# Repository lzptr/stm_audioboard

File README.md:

# stm_audioboard
STM32 based mixed signal audio board from phils lab mixed signal course (https://www.phils-lab.net/courses).

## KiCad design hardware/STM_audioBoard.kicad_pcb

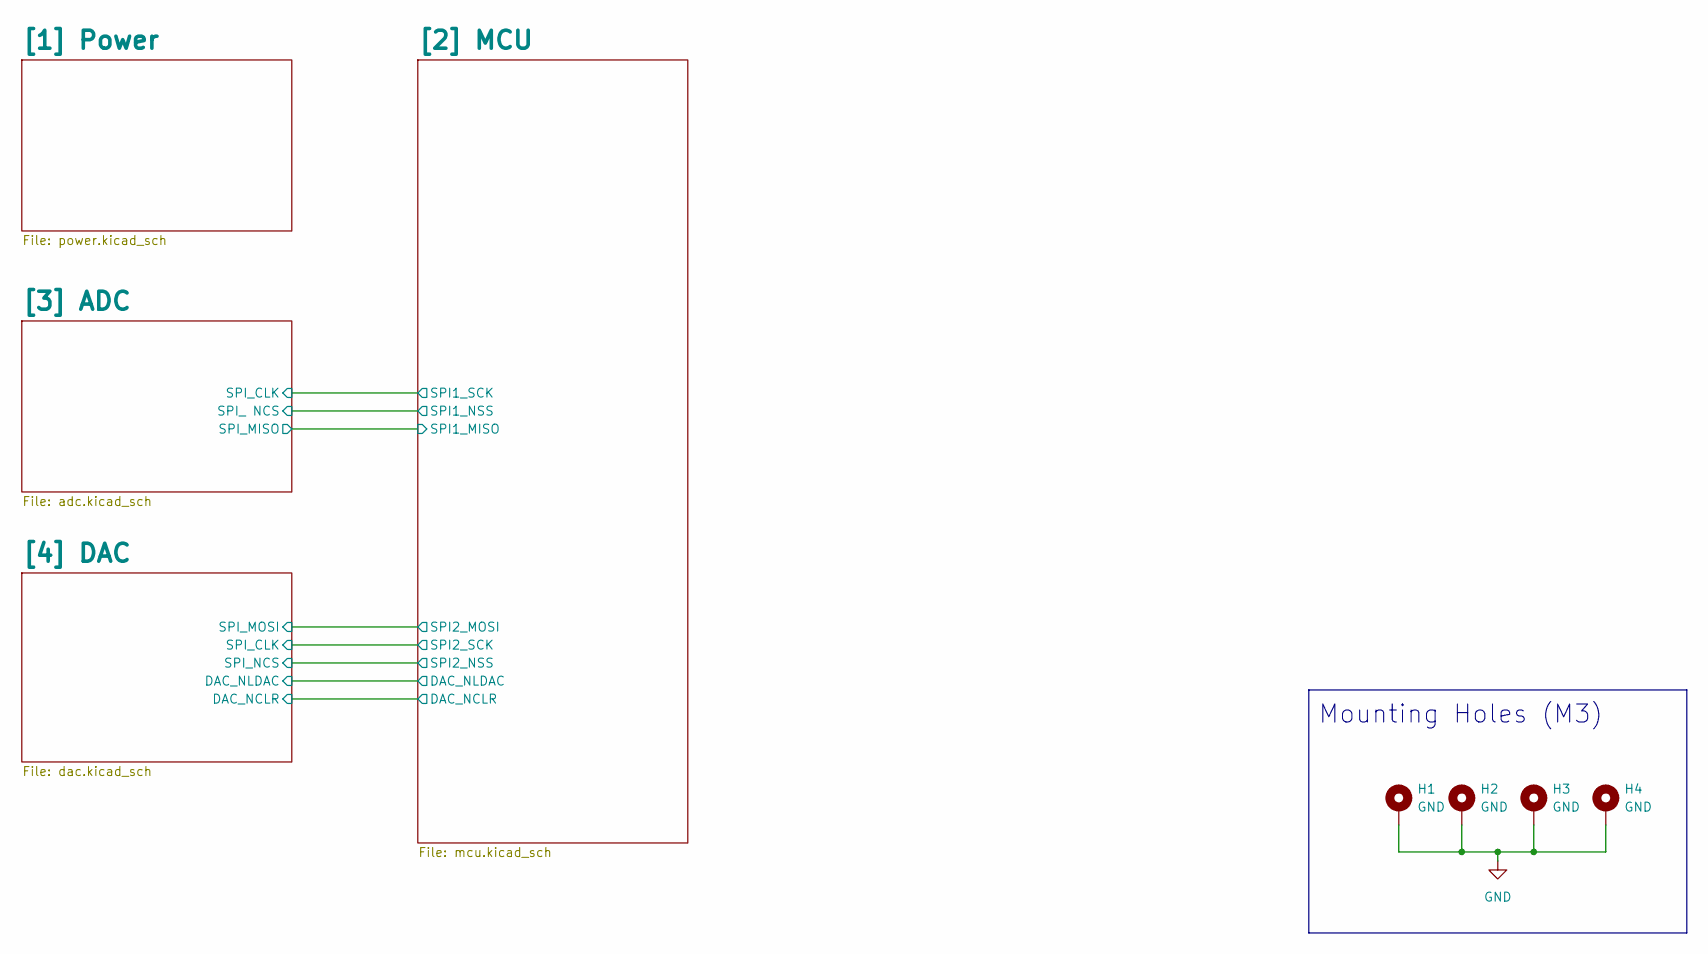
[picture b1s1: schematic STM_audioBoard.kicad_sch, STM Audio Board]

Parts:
H1, H2, H3, H4: GND; MountingHole_3.2mm_M3_Pad

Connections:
GND: H1.1, H2.1, H3.1, H4.1; also elsewhere on the board

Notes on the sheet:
Mounting Holes (M3)

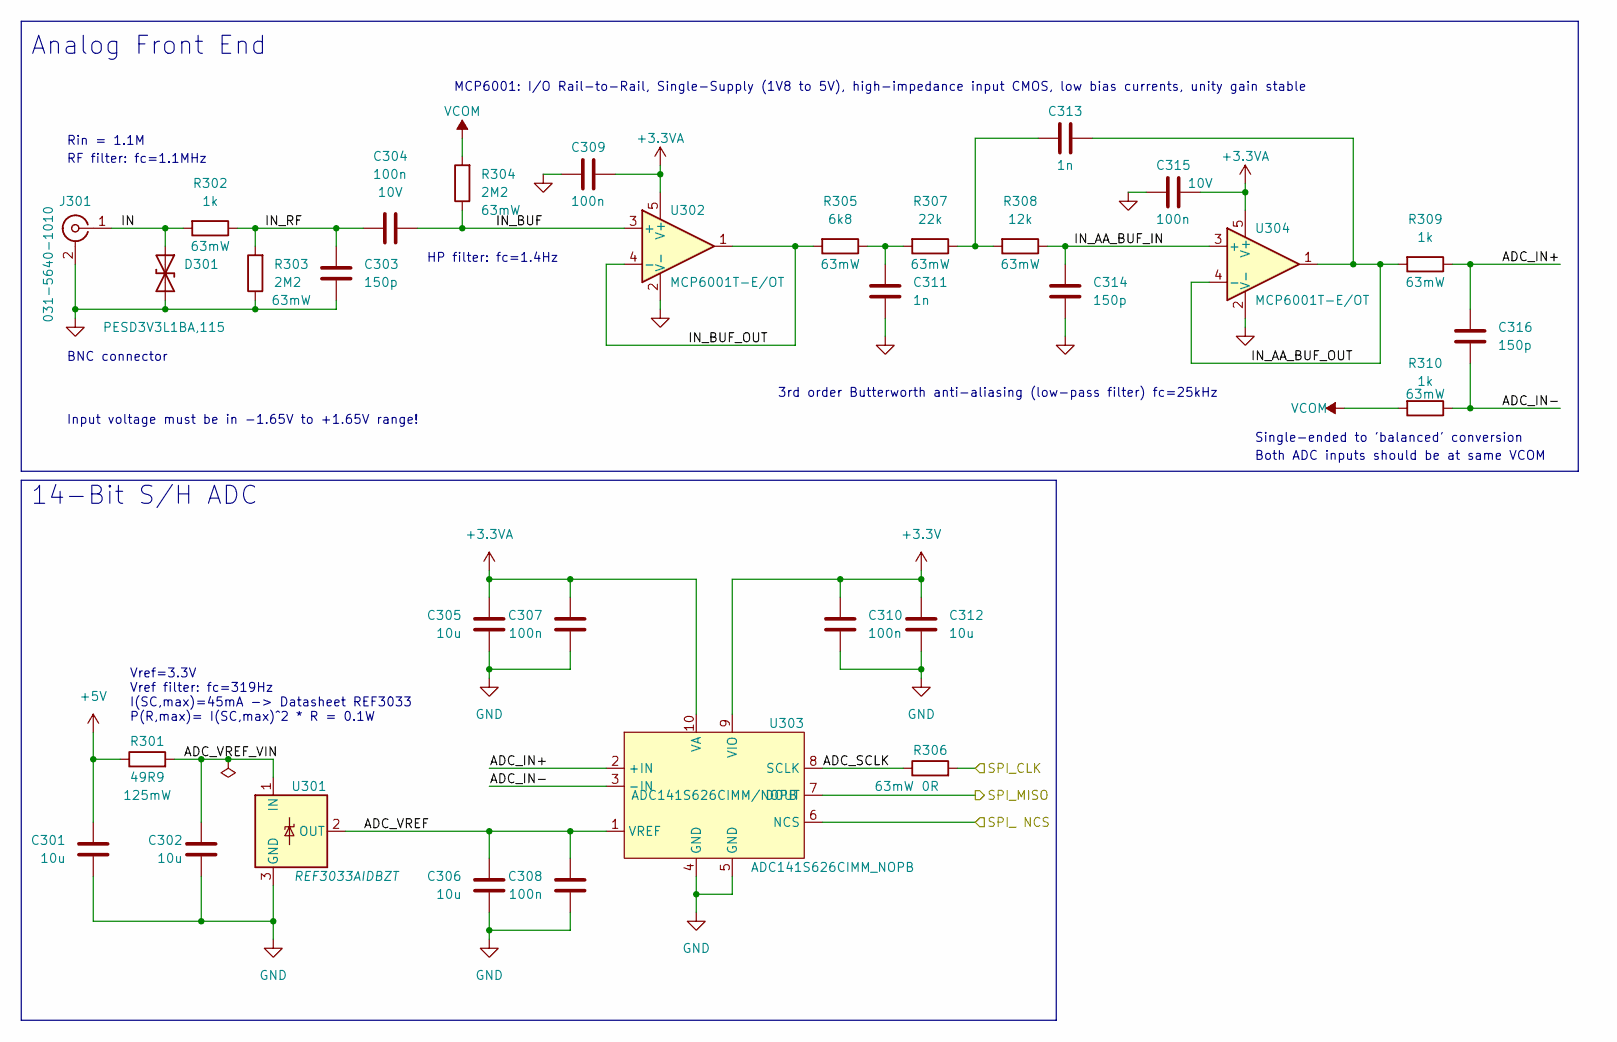
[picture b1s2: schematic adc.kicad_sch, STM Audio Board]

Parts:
C301, C302, C305, C306, C312: 10u; C_0603_1608Metric
C303, C314, C316: 150p; C_0402_1005Metric
C304, C307, C308, C309, C310, C315: 100n; C_0402_1005Metric; Rating 10V; MPN CC0402KRX5R6BB104
C311, C313: 1n; C_0402_1005Metric
D301: PESD3V3L1BA,115; D_SOD-323
J301: 031-5640-1010; AMPHENOL-BNC-031-5640-1010
R301: 49R9; R_0805_2012Metric; Rating 125mW
R302, R309, R310: 1k; R_0402_1005Metric; Rating 63mW
R303, R304: 2M2; R_0402_1005Metric; Rating 63mW
R305: 6k8; R_0402_1005Metric; Rating 63mW
R306: 0R; R_0402_1005Metric; Rating 63mW
R307: 22k; R_0402_1005Metric; Rating 63mW
R308: 12k; R_0402_1005Metric; Rating 63mW
U301: REF3033AIDBZT; SOT-23
U302, U304: MCP6001T-E/OT; SOT-23-5
U303: ADC141S626CIMM_NOPB; VSSOP-10; MPN ADC141S626CIMM/NOPB

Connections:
+3.3V: C310.1, C312.1, U303.9 (VIO); also elsewhere on the board
+3.3VA: C305.1, C307.1, C309.1, C315.1, U302.5 (V+), U303.10 (VA), U304.5 (V+); also elsewhere on the board
+5V: C301.1, R301.1; also elsewhere on the board
/[2] MCU/SPI1_MISO: U303.7 (DOUT); also elsewhere on the board
/[2] MCU/SPI1_NSS: U303.6 (NCS); also elsewhere on the board
/[2] MCU/SPI1_SCK: R306.2; also elsewhere on the board
/[3] ADC/ADC_IN+: C316.1, R309.1, U303.2 (+IN)
/[3] ADC/ADC_IN-: C316.2, R310.1, U303.3 (-IN)
/[3] ADC/ADC_SCLK: R306.1, U303.8 (SCLK)
/[3] ADC/ADC_VREF: C306.1, C308.1, U301.2 (OUT), U303.1 (VREF)
/[3] ADC/ADC_VREF_VIN: C302.1, R301.2, U301.1 (IN)
/[3] ADC/IN: D301.1 (A1), J301.1 (In), R302.2
/[3] ADC/IN_AA_BUF_IN: C314.1, R308.1, U304.3 (+)
/[3] ADC/IN_AA_BUF_OUT: C313.2, R309.2, U304.1, U304.4 (-)
/[3] ADC/IN_BUF: C304.1, R304.1, U302.3 (+)
/[3] ADC/IN_BUF_OUT: R305.2, U302.1, U302.4 (-)
/[3] ADC/IN_RF: C303.1, C304.2, R302.1, R303.2
GND: C301.2, C302.2, C303.2, C305.2, C306.2, C307.2, C308.2, C309.2, C310.2, C311.2, C312.2, C314.2, C315.2, D301.2 (A2), J301.2 (Ext), R303.1, U301.3 (GND), U302.2 (V-), U303.4 (GND), U303.5 (GND), U304.2 (V-); also elsewhere on the board
unnamed: C311.1, R305.1, R307.2
unnamed: C313.1, R307.1, R308.2
VCOM: R304.2, R310.2; also elsewhere on the board

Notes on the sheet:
RF filter: fc=1.1MHz
3rd order Butterworth anti-aliasing (low-pass filter) fc=25kHz
BNC connector
14-Bit S/H ADC
HP filter: fc=1.4Hz
Rin = 1.1M
MCP6001: I/O Rail-to-Rail, Single-Supply (1V8 to 5V), high-impedance input CMOS, low bias currents, unity gain stable
Input voltage must be in -1.65V to +1.65V range!
Vref=3.3V Vref filter: fc=319Hz I(SC,max)=45mA -> Datasheet REF3033 P(R,max)= I(SC,max)^2 * R = 0.1W
Analog Front End
Both ADC inputs should be at same VCOM
Single-ended to 'balanced' conversion

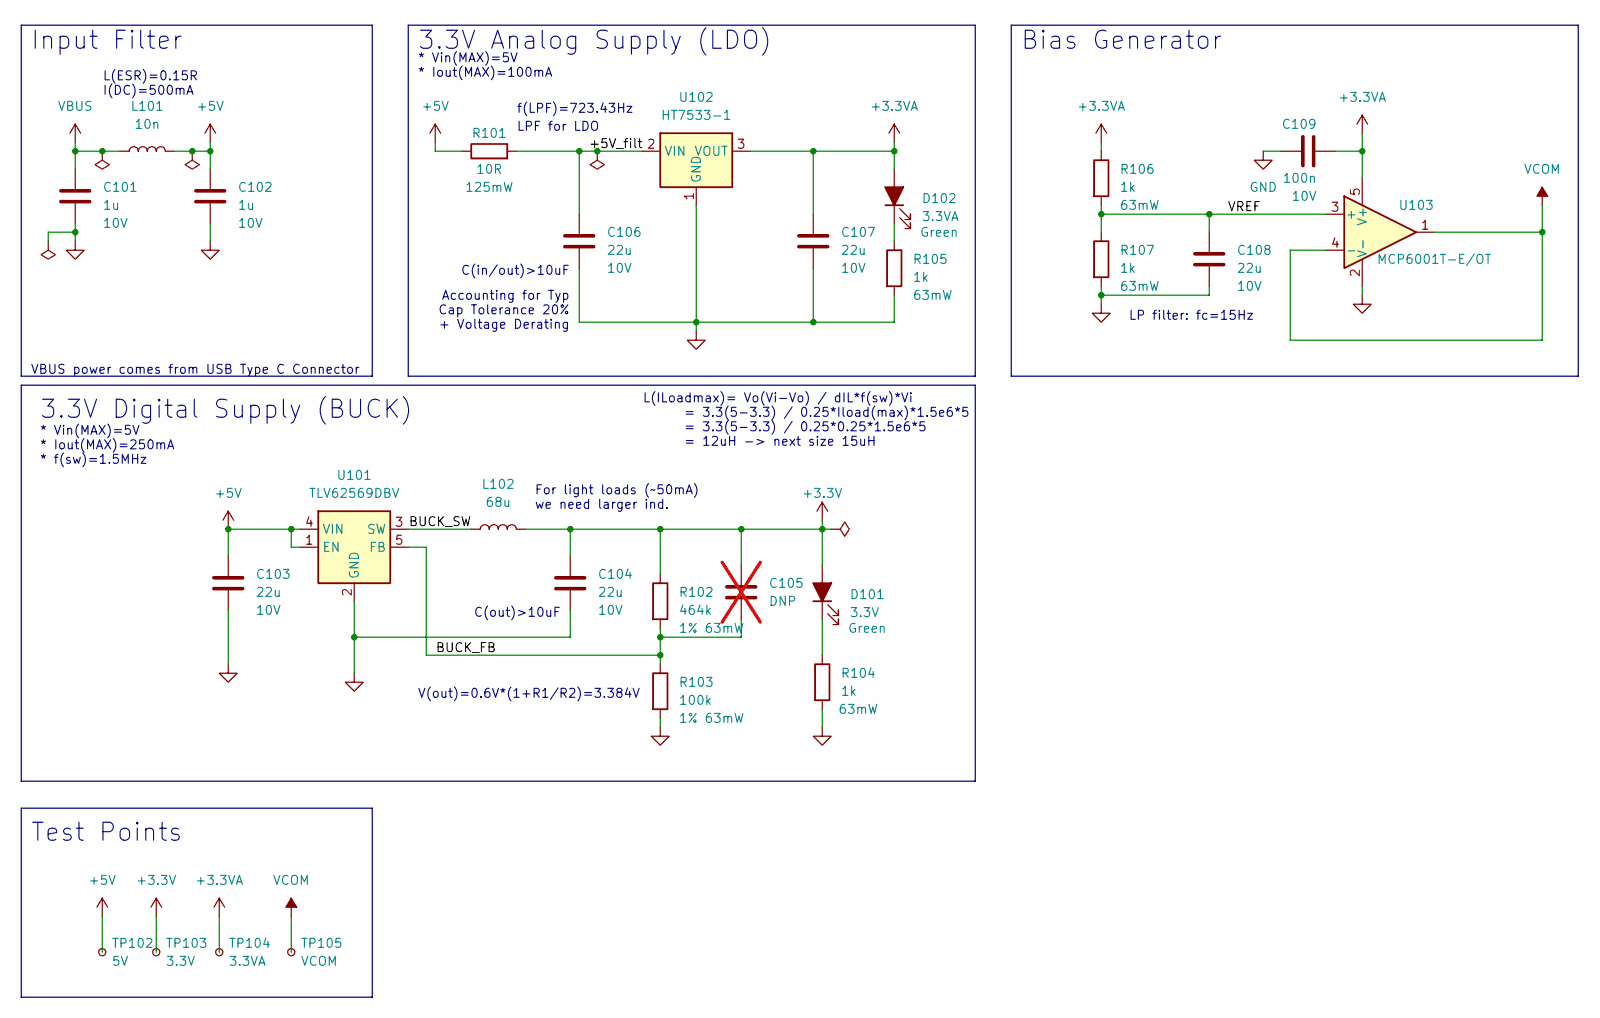
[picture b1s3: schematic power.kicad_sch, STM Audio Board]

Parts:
C101, C102: 1u; C_0603_1608Metric; Rating 10V; MPN CC0603KRX5R6BB105
C103, C104, C106, C107, C108: 22u; C_0805_2012Metric; Rating 10V; MPN CC0805KRX5R6BB225
C105: DNP; C_0402_1005Metric; Rating 10V; not fitted
C109: 100n; C_0402_1005Metric; Rating 10V; MPN CC0402KRX5R6BB104
D101: 3.3V; LED_0603_1608Metric; Rating Green
D102: 3.3VA; LED_0603_1608Metric; Rating Green
L101: 10n; L_0402_1005Metric
L102: 68u; MWSA0603S
R101: 10R; R_0805_2012Metric; Rating 125mW
R102: 464k; R_0402_1005Metric; Rating 1% 63mW
R103: 100k; R_0402_1005Metric; Rating 1% 63mW
R104, R105, R106, R107: 1k; R_0402_1005Metric; Rating 63mW
TP102: 5V; TestPoint_Pad_D1.0mm
TP103: 3.3V; TestPoint_Pad_D1.0mm
TP104: 3.3VA; TestPoint_Pad_D1.0mm
TP105: VCOM; TestPoint_Pad_D1.0mm
U101: TLV62569DBV; SOT-23-5
U102: HT7533-1; SOT-89-3
U103: MCP6001T-E/OT; SOT-23-5

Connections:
+3.3V: C104.1, C105.1, D101.2 (A), L102.2, R102.1, TP103.1; also elsewhere on the board
+3.3VA: C107.1, C109.2, D102.2 (A), R106.1, TP104.1, U102.3 (VOUT), U103.5 (V+); also elsewhere on the board
+5V: C102.1, C103.1, L101.2, R101.1, TP102.1, U101.1 (EN), U101.4 (VIN); also elsewhere on the board
/[1] Power/+5V_filt: C106.1, R101.2, U102.2 (VIN)
/[1] Power/BUCK_FB: C105.2, R102.2, R103.1, U101.5 (FB)
/[1] Power/BUCK_SW: L102.1, U101.3 (SW)
/[1] Power/VREF: C108.1, R106.2, R107.1, U103.3 (+)
GND: C101.2, C102.2, C103.2, C104.2, C106.2, C107.2, C108.2, C109.1, R103.2, R104.2, R105.2, R107.2, U101.2 (GND), U102.1 (GND), U103.2 (V-); also elsewhere on the board
unnamed: D101.1 (K), R104.1
unnamed: D102.1 (K), R105.1
VBUS: C101.1, L101.1; also elsewhere on the board
VCOM: TP105.1, U103.1, U103.4 (-); also elsewhere on the board

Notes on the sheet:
* Vin(MAX)=5V * Iout(MAX)=100mA
Test Points
3.3V Digital Supply (BUCK)
For light loads (~50mA) we need larger ind.
Input Filter
V(out)=0.6V*(1+R1/R2)=3.384V
LP filter: fc=15Hz
Accounting for Typ Cap Tolerance 20% + Voltage Derating
3.3V Analog Supply (LDO)
C(out)>10uF
* Vin(MAX)=5V * Iout(MAX)=250mA * f(sw)=1.5MHz
L(ILoadmax)= Vo(Vi-Vo) / dIL*f(sw)*Vi = 3.3(5-3.3) / 0.25*Iload(max)*1.5e6*5 = 3.3(5-3.3) / 0.25*0.25*1.5e6*5 = 12uH -> next size 15uH
L(ESR)=0.15R I(DC)=500mA
f(LPF)=723.43Hz
Bias Generator
C(in/out)>10uF
VBUS power comes from USB Type C Connector
LPF for LDO

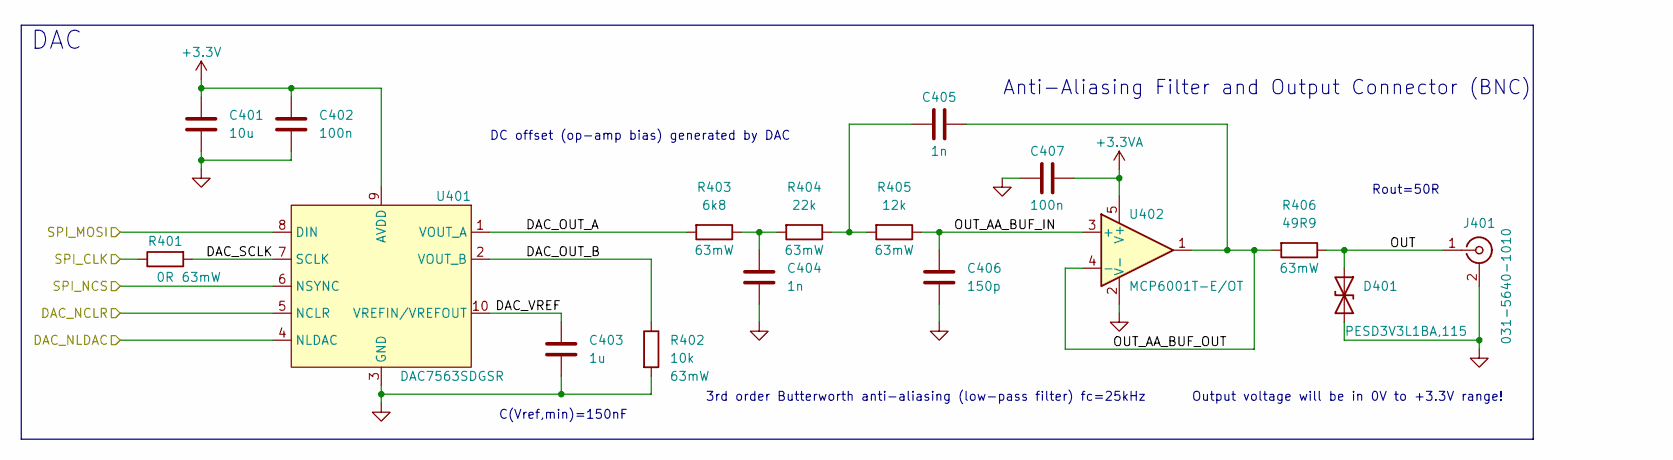
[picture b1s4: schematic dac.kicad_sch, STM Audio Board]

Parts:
C401: 10u; C_0603_1608Metric
C402, C407: 100n; C_0402_1005Metric; Rating 10V; MPN CC0402KRX5R6BB104
C403: 1u; C_0603_1608Metric; Rating 10V; MPN CC0603KRX5R6BB105
C404, C405: 1n; C_0402_1005Metric
C406: 150p; C_0402_1005Metric
D401: PESD3V3L1BA,115; D_SOD-323
J401: 031-5640-1010; AMPHENOL-BNC-031-5640-1010
R401: 0R; R_0402_1005Metric; Rating 63mW
R402: 10k; R_0402_1005Metric; Rating 63mW
R403: 6k8; R_0402_1005Metric; Rating 63mW
R404: 22k; R_0402_1005Metric; Rating 63mW
R405: 12k; R_0402_1005Metric; Rating 63mW
R406: 49R9; R_0402_1005Metric; Rating 63mW
U401: DAC7563SDGSR; VSSOP-10; MPN DAC7563SDGSR
U402: MCP6001T-E/OT; SOT-23-5

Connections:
+3.3V: C401.1, C402.1, U401.9 (AVDD); also elsewhere on the board
+3.3VA: C407.1, U402.5 (V+); also elsewhere on the board
/[2] MCU/DAC_NCLR: U401.5 (NCLR); also elsewhere on the board
/[2] MCU/DAC_NLDAC: U401.4 (NLDAC); also elsewhere on the board
/[2] MCU/SPI2_MOSI: U401.8 (DIN); also elsewhere on the board
/[2] MCU/SPI2_NSS: U401.6 (NSYNC); also elsewhere on the board
/[2] MCU/SPI2_SCK: R401.1; also elsewhere on the board
/[4] DAC/DAC_OUT_A: R403.2, U401.1 (VOUT_A)
/[4] DAC/DAC_OUT_B: R402.1, U401.2 (VOUT_B)
/[4] DAC/DAC_SCLK: R401.2, U401.7 (SCLK)
/[4] DAC/DAC_VREF: C403.1, U401.10 (VREFIN/VREFOUT)
/[4] DAC/OUT: D401.1 (A1), J401.1 (In), R406.1
/[4] DAC/OUT_AA_BUF_IN: C406.1, R405.1, U402.3 (+)
/[4] DAC/OUT_AA_BUF_OUT: C405.2, R406.2, U402.1, U402.4 (-)
GND: C401.2, C402.2, C403.2, C404.2, C406.2, C407.2, D401.2 (A2), J401.2 (Ext), R402.2, U401.3 (GND), U402.2 (V-); also elsewhere on the board
unnamed: C404.1, R403.1, R404.2
unnamed: C405.1, R404.1, R405.2

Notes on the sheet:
DC offset (op-amp bias) generated by DAC
Rout=50R
Output voltage will be in 0V to +3.3V range!
C(Vref,min)=150nF
Anti-Aliasing Filter and Output Connector (BNC)
3rd order Butterworth anti-aliasing (low-pass filter) fc=25kHz
DAC

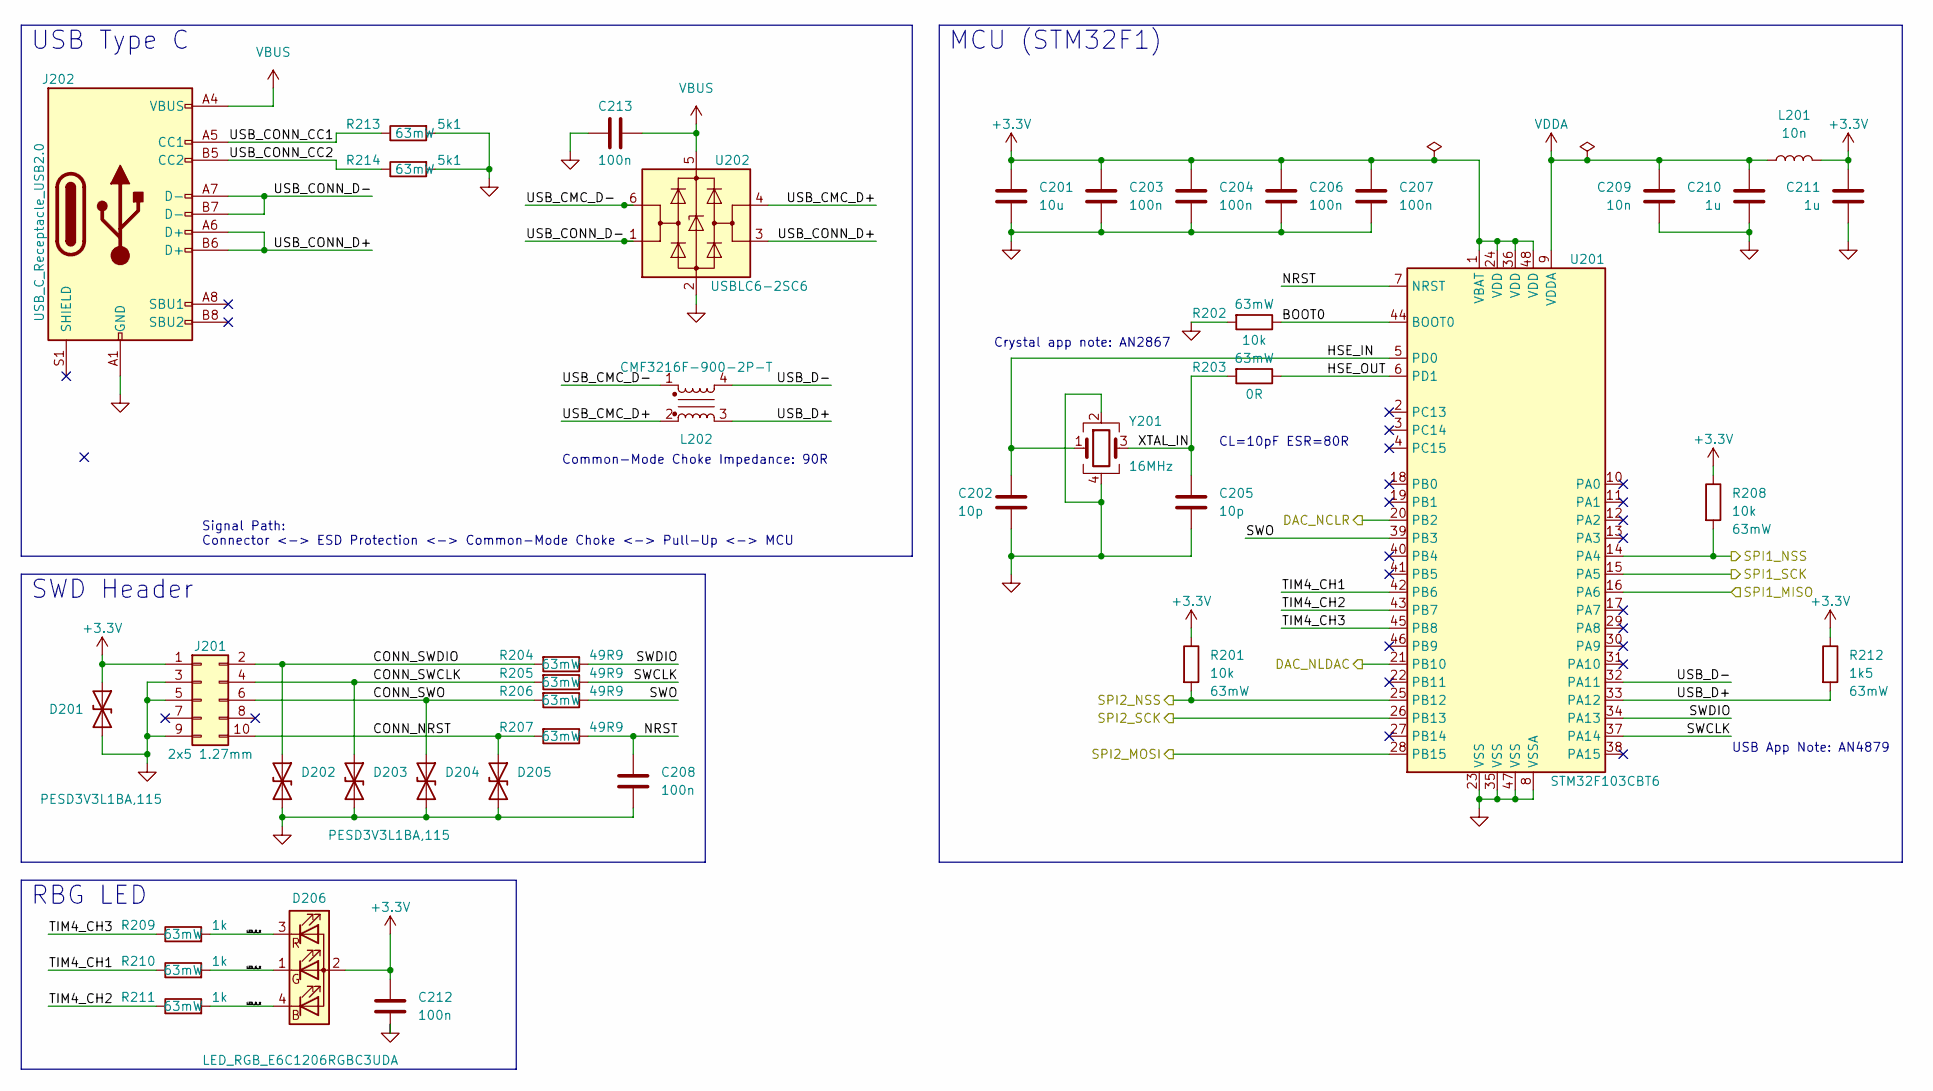
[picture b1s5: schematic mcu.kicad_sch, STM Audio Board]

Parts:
C201: 10u; C_0603_1608Metric
C202, C205: 10p; C_0402_1005Metric
C203, C204, C206, C207, C208, C212, C213: 100n; C_0402_1005Metric; Rating 10V; MPN CC0402KRX5R6BB104
C209: 10n; C_0402_1005Metric
C210, C211: 1u; C_0603_1608Metric; Rating 10V; MPN CC0603KRX5R6BB105
D201, D202, D203, D204, D205: PESD3V3L1BA,115; D_SOD-323
D206: LED_RGB_E6C1206RGBC3UDA; LED_Cree-PLCC4_2x2mm_CW
J201: 2x5 1.27mm; PinHeader_2x05_P1.27mm_Vertical_SMD
J202: USB_C_Receptacle_USB2.0; USB_C_Receptacle_HRO_TYPE-C-31-M-12
L201: 10n; L_0402_1005Metric
L202: CMF3216F-900-2P-T; CMC-1206
R201, R202, R208: 10k; R_0402_1005Metric; Rating 63mW
R203: 0R; R_0402_1005Metric; Rating 63mW
R204, R205, R206, R207: 49R9; R_0402_1005Metric; Rating 63mW
R209, R210, R211: 1k; R_0402_1005Metric; Rating 63mW
R212: 1k5; R_0402_1005Metric; Rating 63mW
R213, R214: 5k1; R_0402_1005Metric; Rating 63mW
U201: STM32F103CBT6; LQFP-48_7x7mm_P0.5mm; Manufacturer Part Number STM32F103CBT6
U202: USBLC6-2SC6; SOT-23-6
Y201: 16MHz; Crystal_SMD_3225-4Pin_3.2x2.5mm

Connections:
+3.3V: C201.1, C203.1, C204.1, C206.1, C207.1, C211.1, C212.1, D201.1 (A1), D206.2 (A), J201.1, L201.2, R201.1, R208.1, R212.1, U201.1 (VBAT), U201.24 (VDD), U201.36 (VDD), U201.48 (VDD); also elsewhere on the board
/[2] MCU/BOOT0: R202.1, U201.44 (BOOT0)
/[2] MCU/CONN_NRST: D205.1 (A1), J201.10, R207.2
/[2] MCU/CONN_SWCLK: D203.1 (A1), J201.4, R205.2
/[2] MCU/CONN_SWDIO: D202.1 (A1), J201.2, R204.2
/[2] MCU/CONN_SWO: D204.1 (A1), J201.6, R206.2
/[2] MCU/DAC_NCLR: U201.20 (PB2); also elsewhere on the board
/[2] MCU/DAC_NLDAC: U201.21 (PB10); also elsewhere on the board
/[2] MCU/HSE_IN: C202.1, U201.5 (PD0), Y201.1
/[2] MCU/HSE_OUT: R203.1, U201.6 (PD1)
/[2] MCU/LED_B_K: D206.4 (BK), R211.2
/[2] MCU/LED_G_K: D206.1 (GK), R210.2
/[2] MCU/LED_R_K: D206.3 (RK), R209.2
/[2] MCU/NRST: C208.1, R207.1, U201.7 (NRST)
/[2] MCU/SPI1_MISO: U201.16 (PA6); also elsewhere on the board
/[2] MCU/SPI1_NSS: R208.2, U201.14 (PA4); also elsewhere on the board
/[2] MCU/SPI1_SCK: U201.15 (PA5); also elsewhere on the board
/[2] MCU/SPI2_MOSI: U201.28 (PB15); also elsewhere on the board
/[2] MCU/SPI2_NSS: R201.2, U201.25 (PB12); also elsewhere on the board
/[2] MCU/SPI2_SCK: U201.26 (PB13); also elsewhere on the board
/[2] MCU/SWCLK: R205.1, U201.37 (PA14)
/[2] MCU/SWDIO: R204.1, U201.34 (PA13)
/[2] MCU/SWO: R206.1, U201.39 (PB3)
/[2] MCU/TIM4_CH1: R210.1, U201.42 (PB6)
/[2] MCU/TIM4_CH2: R211.1, U201.43 (PB7)
/[2] MCU/TIM4_CH3: R209.1, U201.45 (PB8)
/[2] MCU/USB_CMC_D+: L202.2, U202.4 (I/O2)
/[2] MCU/USB_CMC_D-: L202.1, U202.6 (I/O1)
/[2] MCU/USB_CONN_CC1: J202.A5 (CC1), R213.1
/[2] MCU/USB_CONN_CC2: J202.B5 (CC2), R214.1
/[2] MCU/USB_CONN_D+: J202.A6 (D+), J202.B6 (D+), U202.3 (I/O2)
/[2] MCU/USB_CONN_D-: J202.A7 (D-), J202.B7 (D-), U202.1 (I/O1)
/[2] MCU/USB_D+: L202.3, R212.2, U201.33 (PA12)
/[2] MCU/USB_D-: L202.4, U201.32 (PA11)
/[2] MCU/XTAL_IN: C205.1, R203.2, Y201.3
GND: C201.2, C202.2, C203.2, C204.2, C205.2, C206.2, C207.2, C208.2, C209.2, C210.2, C211.2, C212.2, C213.2, D201.2 (A2), D202.2 (A2), D203.2 (A2), D204.2 (A2), D205.2 (A2), J201.3, J201.5, J201.9, J202.A1 (GND), J202.A12 (GND), J202.B1 (GND), J202.B12 (GND), R202.2, R213.2, R214.2, U201.8 (VSSA), U201.23 (VSS), U201.35 (VSS), U201.47 (VSS), U202.2 (GND), Y201.2, Y201.4; also elsewhere on the board
VBUS: C213.1, J202.A4 (VBUS), J202.A9 (VBUS), J202.B4 (VBUS), J202.B9 (VBUS), U202.5 (VBUS); also elsewhere on the board
VDDA: C209.1, C210.1, L201.1, U201.9 (VDDA)

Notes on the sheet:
USB Type C
CL=10pF ESR=80R
USB App Note: AN4879
RBG LED
Signal Path: Connector <-> ESD Protection <-> Common-Mode Choke <-> Pull-Up <-> MCU
SWD Header
Crystal app note: AN2867
Common-Mode Choke Impedance: 90R
MCU (STM32F1)

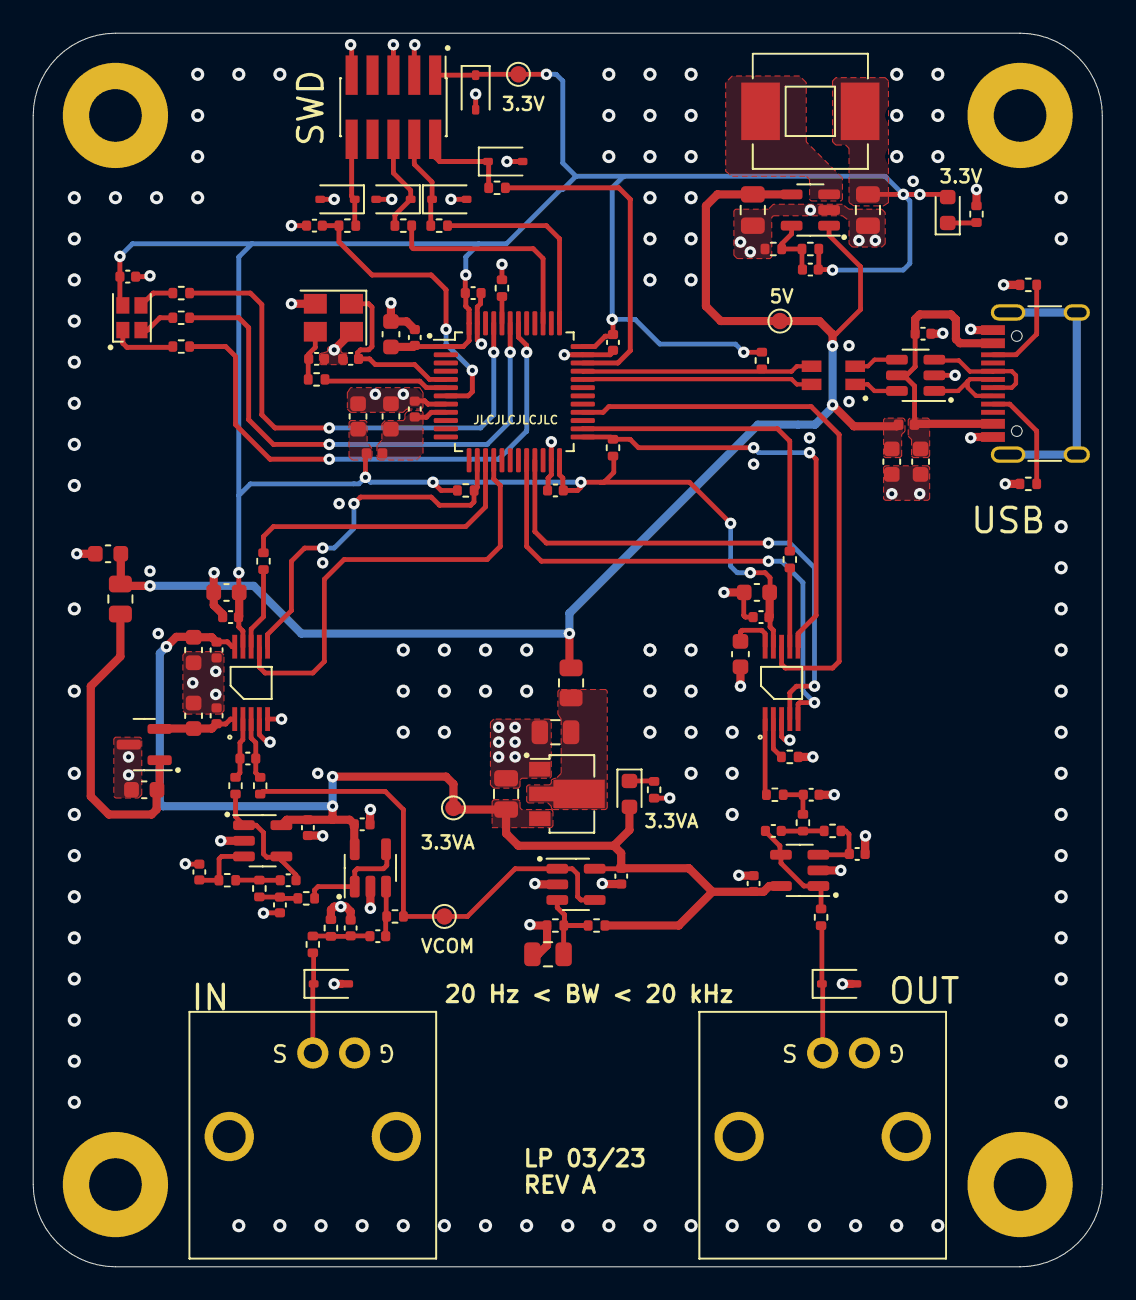
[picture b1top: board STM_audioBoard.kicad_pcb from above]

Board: 4 copper layers, 65.0 x 75.0 mm, 120 parts (0 on the bottom side), 69 nets.

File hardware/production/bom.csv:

Designator,Footprint,Quantity,Value,LCSC Part #
"C101, C102, C210, C211, C403",0603,5,1u,CC0603KRX5R6BB105
"C103, C104, C106, C107, C108",0805,5,22u,CC0805KRX5R6BB225
C105,0402,1,DNP,
"C109, C203, C204, C206, C207, C208, C212, C213, C304, C307, C308, C309, C310, C315, C402, C407",0402,16,100n,CC0402KRX5R6BB104
"C201, C301, C302, C305, C306, C312, C401",0603,7,10u,
"C202, C205",0402,2,10p,
"C209, L101, L201",0402,3,10n,
"C303, C314, C316, C406",0402,4,150p,
"C311, C313, C404, C405",0402,4,1n,
D101,0603,1,3.3V,
D102,0603,1,3.3VA,
"D201, D202, D203, D204, D205, D301, D401",D_SOD-323,7,"PESD3V3L1BA,115",
D206,LED_Cree-PLCC4_2x2mm_CW,1,LED_RGB_E6C1206RGBC3UDA,
"H1, H2, H3, H4",MountingHole_3.2mm_M3_Pad,4,GND,
J201,PinHeader_2x05_P1.27mm_Vertical_SMD,1,2x5 1.27mm,
J202,USB_C_Receptacle_HRO_TYPE-C-31-M-12,1,USB_C_Receptacle_USB2.0,
"J301, J401",AMPHENOL-BNC-031-5640-1010,2,031-5640-1010,
L102,MWSA0603S,1,68u,
L202,CMC-1206,1,CMF3216F-900-2P-T,
R101,0805,1,10R,
R102,0402,1,464k,
R103,0402,1,100k,
"R104, R105, R106, R107, R209, R210, R211, R302, R309, R310",0402,10,1k,
"R201, R202, R208, R402",0402,4,10k,
"R203, R306, R401",0402,3,0R,
"R204, R205, R206, R207, R406",0402,5,49R9,
R212,0402,1,1k5,
"R213, R214",0402,2,5k1,
R301,0805,1,49R9,
"R303, R304",0402,2,2M2,
"R305, R403",0402,2,6k8,
"R307, R404",0402,2,22k,
"R308, R405",0402,2,12k,
TP102,TestPoint_Pad_D1.0mm,1,5V,
TP103,TestPoint_Pad_D1.0mm,1,3.3V,
TP104,TestPoint_Pad_D1.0mm,1,3.3VA,
TP105,TestPoint_Pad_D1.0mm,1,VCOM,
U101,SOT-23-5,1,TLV62569DBV,
U102,SOT-89-3,1,HT7533-1,
"U103, U302, U304, U402",SOT-23-5,4,MCP6001T-E/OT,
U201,LQFP-48_7x7mm_P0.5mm,1,STM32F103CBT6,
U202,SOT-23-6,1,USBLC6-2SC6,
U301,SOT-23,1,REF3033AIDBZT,
U303,VSSOP-10,1,ADC141S626CIMM_NOPB,
U401,VSSOP-10,1,DAC7563SDGSR,
Y201,Crystal_SMD_3225-4Pin_3.2x2.5mm,1,16MHz,

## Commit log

2023-04-19 Finished course project
